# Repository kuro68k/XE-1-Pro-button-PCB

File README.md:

# XE-1-Pro-button-PCB

Replacement PCB for the buttons on the XE-1 Pro joystick, which takes standard "Cherry MX" mount keyboard switches. The original uses some other kind of keyboard switch. Now you can have your preferred weight and tactility.

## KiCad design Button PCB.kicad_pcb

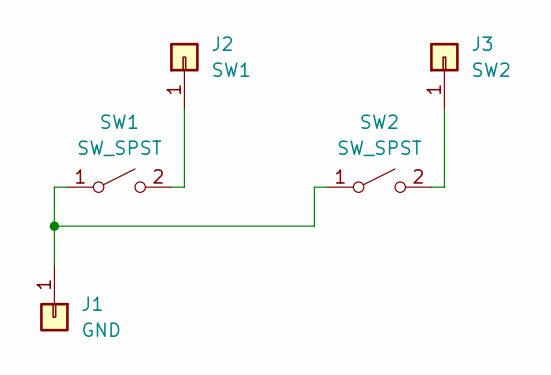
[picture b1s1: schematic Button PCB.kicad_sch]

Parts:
J1: GND; TestPoint_THTPad_D3.0mm_Drill1.5mm
J2: SW1; TestPoint_THTPad_D3.0mm_Drill1.5mm
J3: SW2; TestPoint_THTPad_D3.0mm_Drill1.5mm
SW1, SW2: SW_SPST; SW_Cherry_MX_1.00u_PCB

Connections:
unnamed: J1.1, SW1.1 (A), SW2.1 (A)
unnamed: J2.1, SW1.2 (B)
unnamed: J3.1, SW2.2 (B)

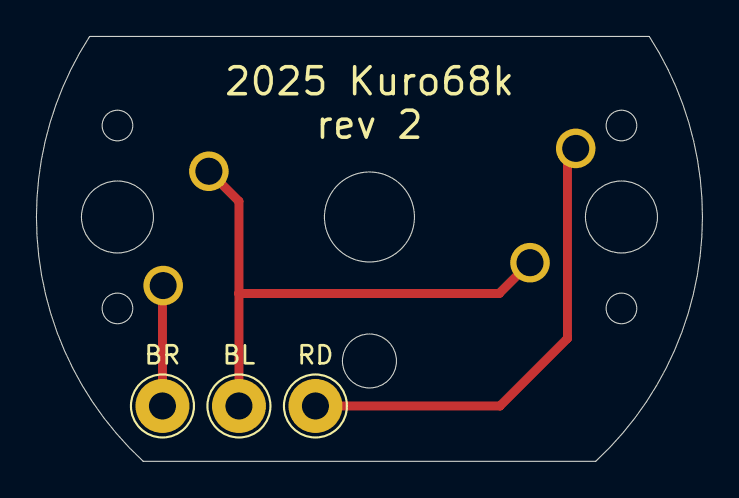
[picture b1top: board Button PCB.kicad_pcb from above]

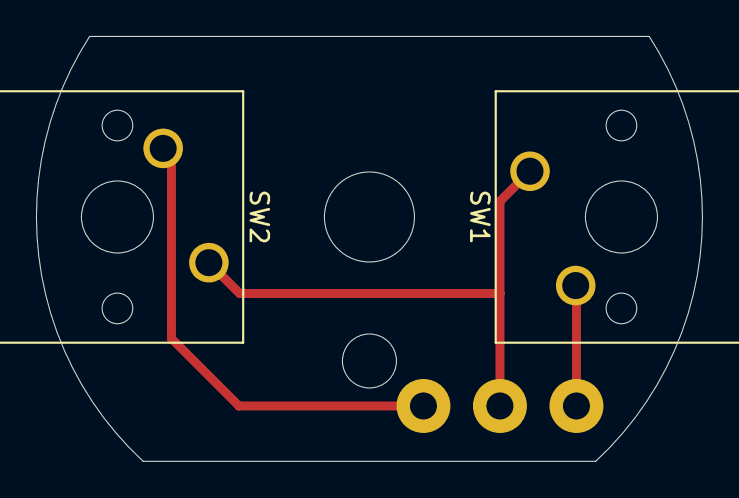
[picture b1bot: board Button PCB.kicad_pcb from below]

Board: 2 copper layers, 37.0 x 23.6 mm, 5 parts (2 on the bottom side), 3 nets.
